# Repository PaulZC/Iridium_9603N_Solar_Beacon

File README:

########################################
# Iridium 9603N Solar Beacon Prototype #
########################################

A breadboard prototype for a Solar Powered Iridium 9603N Beacon.

Power for the beacon is provided by a PowerFilm MPT3.6-150 solar panel.

Power for the Iridium 9603N is provided by a Linear Technology LTC3225EDDB supercapacitor charger.

See Iridium_9603N_Solar_Beacon_Prototype.pdf for a full description of the project:
https://github.com/PaulZC/Iridium_9603N_Solar_Beacon/blob/master/Iridium_9603N_Solar_Beacon_Prototype.pdf

The Arduino code can be found in Iridium9603NSolarBeaconPrototype
https://github.com/PaulZC/Iridium_9603N_Solar_Beacon/tree/master/Iridium9603NSolarBeaconPrototype

A Fritzing hook-up diagram can be found in Iridium_9603N_Solar_Beacon_Prototype_Fritzing.png
https://github.com/PaulZC/Iridium_9603N_Solar_Beacon/blob/master/Iridium_9603N_Solar_Beacon_Prototype_Fritzing.png

This project is distributed under a Creative Commons Attribution + Share-alike (BY-SA) licence.

Enjoy!

Paul

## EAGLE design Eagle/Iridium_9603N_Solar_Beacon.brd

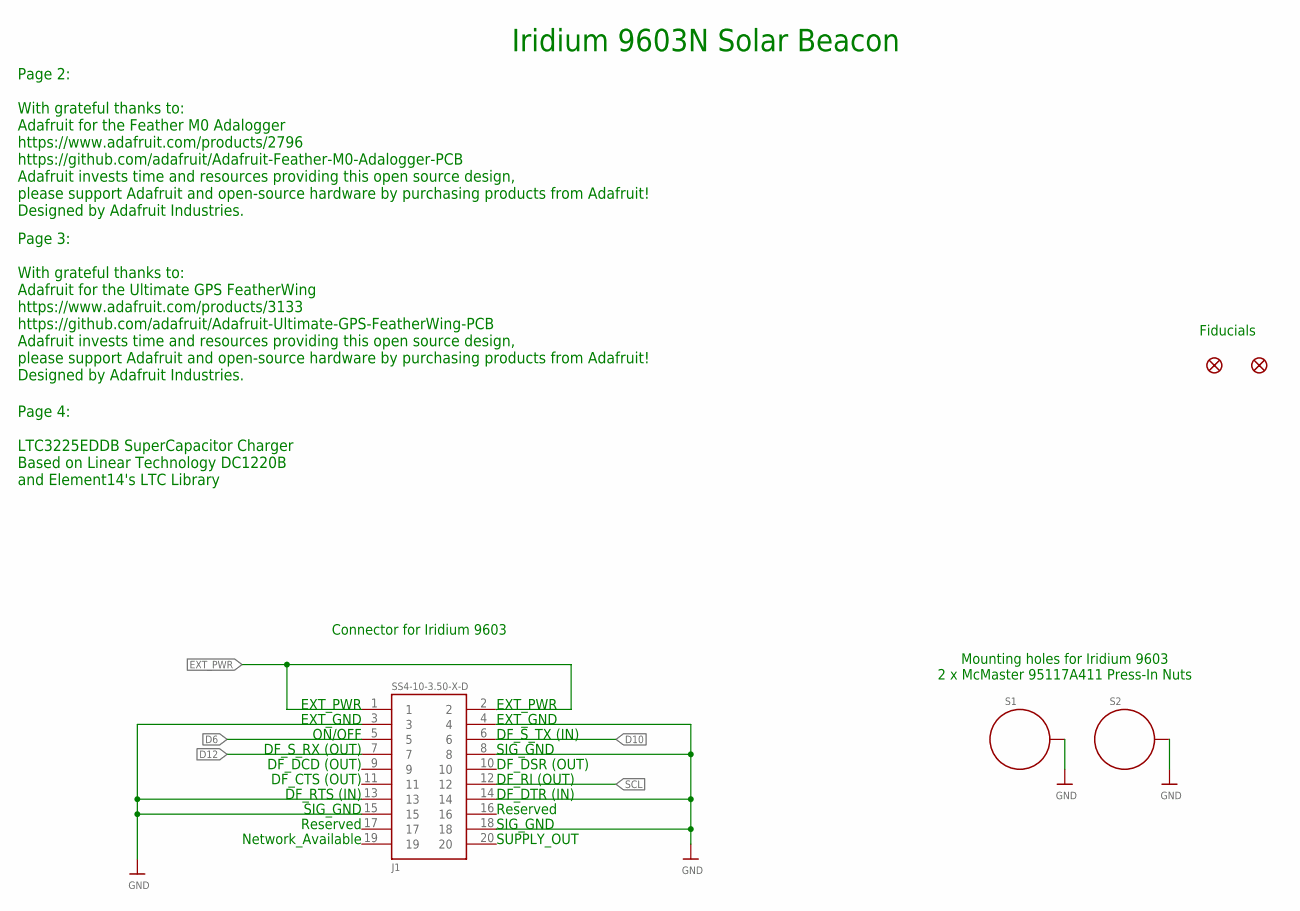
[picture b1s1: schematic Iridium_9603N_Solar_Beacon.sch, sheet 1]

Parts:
FD1, FD2: FIDUCIAL1X2; FIDUCIAL-1X2
J1: SS4-10-3.50-X-D
S1, S2: STANDOFF_ELECTRICALMCMASTER-95117A411; STANDOFF-ELECTRICAL-MCMASTER-95117A411

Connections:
D6: J1.5; also elsewhere on the board
D10: J1.6; also elsewhere on the board
D12: J1.7; also elsewhere on the board
EXT_PWR: J1.1, J1.2; also elsewhere on the board
GND: J1.3, J1.4, J1.8, J1.13, J1.14, J1.15, J1.18, S1.P1, S2.P1; also elsewhere on the board
SCL: J1.12; also elsewhere on the board

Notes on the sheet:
Connector for Iridium 9603
Mounting holes for Iridium 9603 2 x McMaster 95117A411 Press-In Nuts
Iridium 9603N Solar Beacon
Page 2: With grateful thanks to: Adafruit for the Feather M0 Adalogger https://www.adafruit.com/products/2796 https://github.com/adafruit/Adafruit-Feather-M0-Adalogger-PCB Adafruit invests time and resources providing this open source design, please support Adafruit and open-source hardware by purc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
Page 3: With grateful thanks to: Adafruit for the Ultimate GPS FeatherWing https://www.adafruit.com/products/3133 https://github.com/adafruit/Adafruit-Ultimate-GPS-FeatherWing-PCB Adafruit invests time and resources providing this open source design, please support Adafruit and open-source hardware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
EXT_PWR
EXT_GND
ON/OFF
DF_S_RX (OUT)
DF_DCD (OUT)
DF_CTS (OUT)
DF_RTS (IN)
SIG_GND
Reserved
Network_Available
DF_S_TX (IN)
DF_DSR (OUT)
DF_RI (OUT)
DF_DTR (IN)
SUPPLY_OUT
Page 4: LTC3225EDDB SuperCapacitor Charger Based on Linear Technology DC1220B and Element14's LTC Library
Fiducials

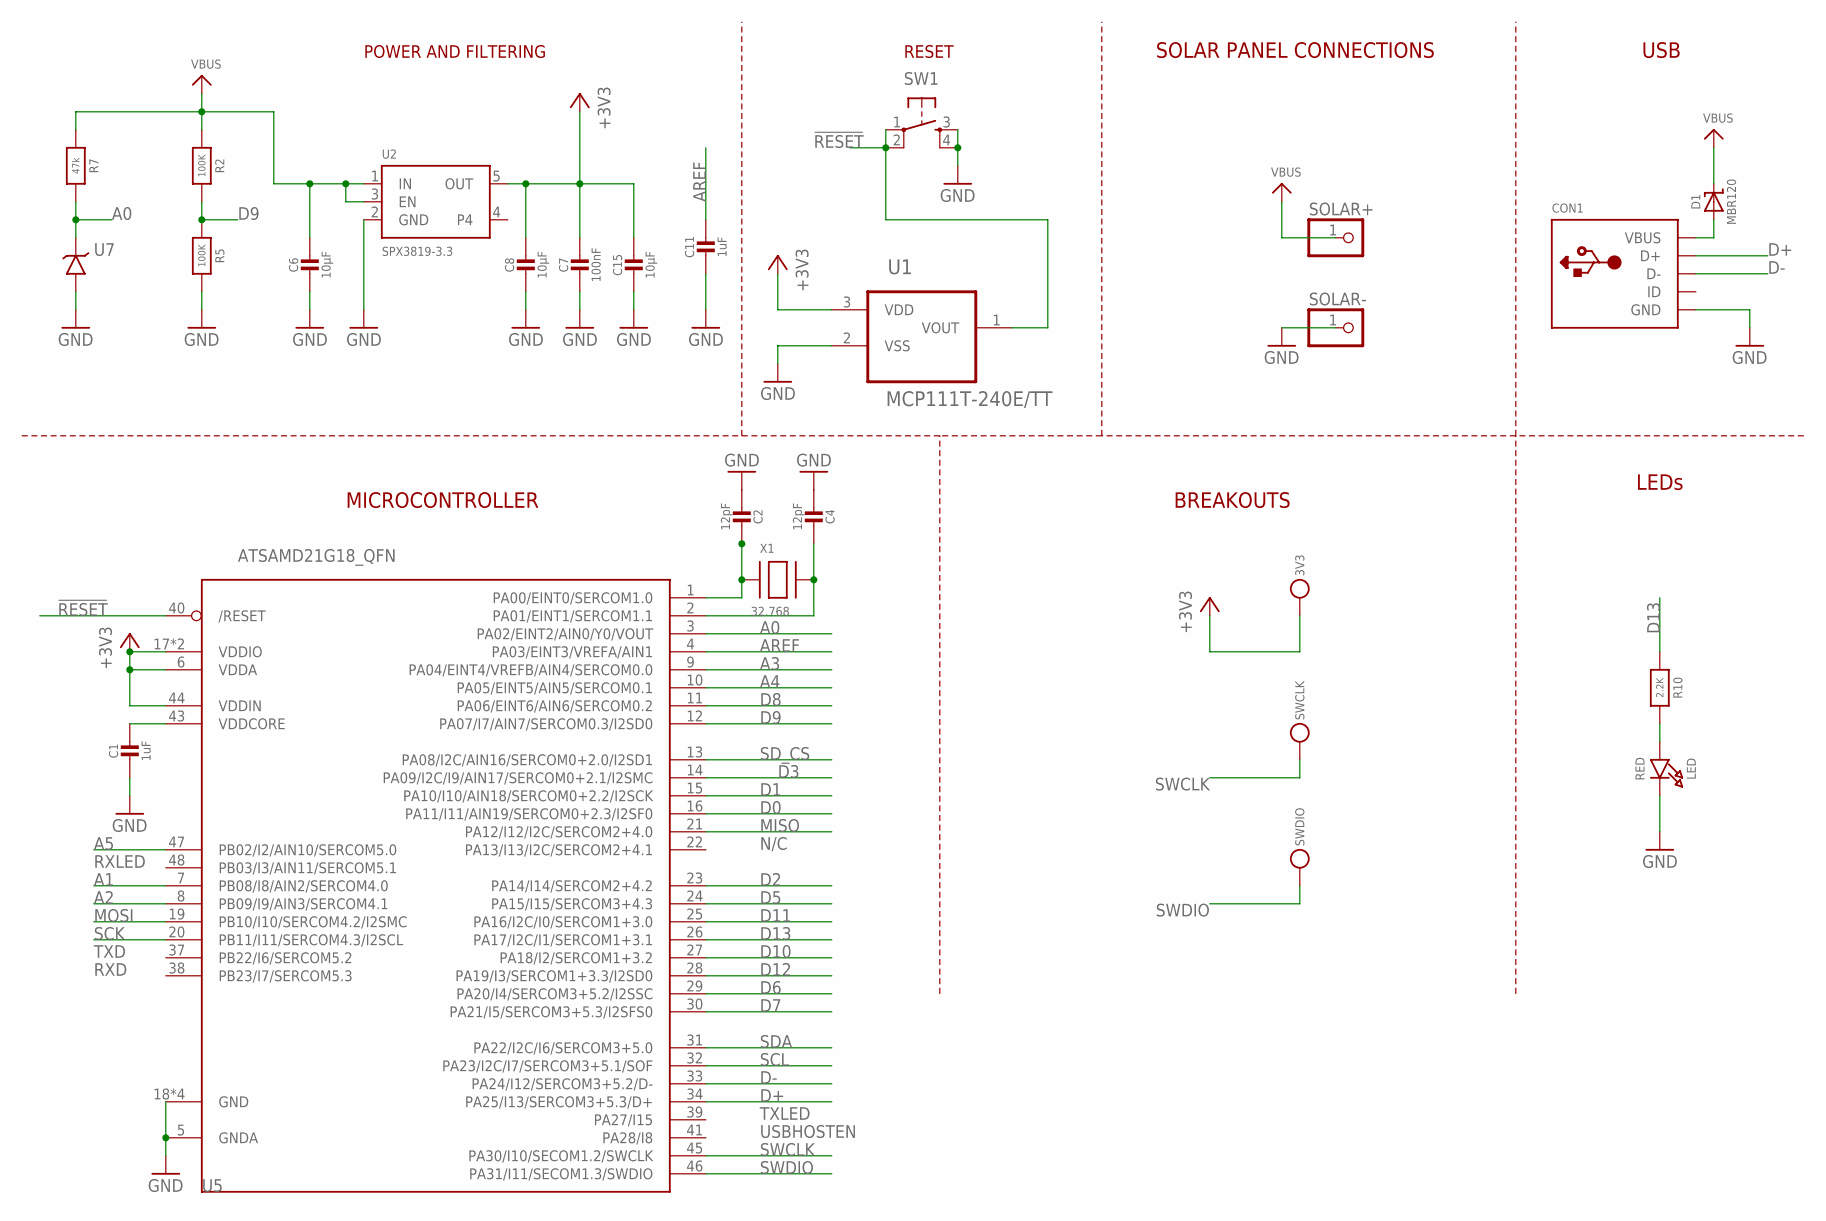
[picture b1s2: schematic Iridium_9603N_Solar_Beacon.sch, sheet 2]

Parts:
3V3: TESTPOINTROUND1.5MM; TESTPOINT_ROUND_1.5MM
C1, C11: 1uF; 0603-NO
C2, C4: 12pF; 0603-NO
C6, C8, C15: 10µF; 0805-NO
C7: 100nF; 0603-NO
CON1: MICROBUILDER_USBFCI_10103594_CORRECTED; MICROBUILDER_FCI_10103594_CORRECTED
D1: MBR120; SOD-123
LED: RED; CHIPLED_0805_NOOUTLINE
R2, R5: 100K; 0603-NO
R7: 47k; 0603-NO
R10: 2.2K; 0603-NO
SOLAR+: PINHD-1X1; 1X01
SOLAR-: PINHD-1X1; 1X01
SW1: SWITCH_SPST_4_PINRECT; TACTILE_SWITCH_SMD_4.6X2.8MM
SWCLK: TESTPOINTROUND1.5MM; TESTPOINT_ROUND_1.5MM
SWDIO: TESTPOINTROUND1.5MM; TESTPOINT_ROUND_1.5MM
U1: MCP111T-240E/TT; SOT95P237X112-3N; MPN MCP111T-240E/TT
U2: SPX3819-3.3; SOT23-5
U5: ATSAMD21G18_QFN; TQFN48_7MM
U7: LT1634-1,25BMCMS8; MSOP8
X1: 32.768; XTAL3215

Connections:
!RESET: SW1.1, SW1.2, U1.1 (VOUT), U5.40 (/RESET)
+3V3: 3V3.P$1, C7.1, C8.1, C15.1, U1.3 (VDD), U2.5 (OUT), U5.6 (VDDA), U5.17 (VDDIO), U5.36 (VDDIO), U5.44 (VDDIN); also elsewhere on the board
A0: R7.2, U5.3 (PA02/EINT2/AIN0/Y0/VOUT), U7.6 (VOUT)
A1: U5.7 (PB08/I8/AIN2/SERCOM4.0); also elsewhere on the board
A2: U5.8 (PB09/I9/AIN3/SERCOM4.1)
A3: U5.9 (PA04/EINT4/VREFB/AIN4/SERCOM0.0)
A4: U5.10 (PA05/EINT5/AIN5/SERCOM0.1)
A5: U5.47 (PB02/I2/AIN10/SERCOM5.0)
AREF: C11.1, U5.4 (PA03/EINT3/VREFA/AIN1)
D0: U5.16 (PA11/I11/AIN19/SERCOM0+2.3/I2SF0); also elsewhere on the board
D1: U5.15 (PA10/I10/AIN18/SERCOM0+2.2/I2SCK); also elsewhere on the board
D2: U5.23 (PA14/I14/SERCOM2+4.2)
D3: U5.14 (PA09/I2C/I9/AIN17/SERCOM0+2.1/I2SMC)
D5: U5.24 (PA15/I15/SERCOM3+4.3); also elsewhere on the board
D6: U5.29 (PA20/I4/SERCOM3+5.2/I2SSC); also elsewhere on the board
D7: U5.30 (PA21/I5/SERCOM3+5.3/I2SFS0)
D8: U5.11 (PA06/EINT6/AIN6/SERCOM0.2)
D9: R2.2, R5.1, U5.12 (PA07/I7/AIN7/SERCOM0.3/I2SD0)
D10: U5.27 (PA18/I2/SERCOM1+3.2); also elsewhere on the board
D11: U5.25 (PA16/I2C/I0/SERCOM1+3.0); also elsewhere on the board
D12: U5.28 (PA19/I3/SERCOM1+3.3/I2SD0); also elsewhere on the board
D13: R10.1, U5.26 (PA17/I2C/I1/SERCOM1+3.1)
D+: CON1.D+, U5.34 (PA25/I13/SERCOM3+5.3/D+)
D-: CON1.D-, U5.33 (PA24/I12/SERCOM3+5.2/D-)
GND: C1.2, C2.2, C4.2, C6.2, C7.2, C8.2, C11.2, C15.2, CON1.BASE@1 (GND), CON1.BASE@2 (GND), CON1.GND, CON1.SPRT@1 (GND), CON1.SPRT@2 (GND), CON1.SPRT@3 (GND), CON1.SPRT@4 (GND), LED.C, R5.2, SOLAR-.1, SW1.3, SW1.4, U1.2 (VSS), U2.2 (GND), U5.5 (GNDA), U5.18 (GND), U5.35 (GND), U5.42 (GND), U5.THERMAL (GND), U7.4 (GND); also elsewhere on the board
MISO: U5.21 (PA12/I12/I2C/SERCOM2+4.0); also elsewhere on the board
MOSI: U5.19 (PB10/I10/SERCOM4.2/I2SMC)
unnamed: LED.A, R10.2
unnamed: C2.1, U5.1 (PA00/EINT0/SERCOM1.0), X1.P$1
unnamed: C4.1, U5.2 (PA01/EINT1/SERCOM1.1), X1.P$2
unnamed: CON1.VBUS, D1.A
SCK: U5.20 (PB11/I11/SERCOM4.3/I2SCL)
SCL: U5.32 (PA23/I2C/I7/SERCOM3+5.1/SOF); also elsewhere on the board
SDA: U5.31 (PA22/I2C/I6/SERCOM3+5.0)
SD_CS: U5.13 (PA08/I2C/AIN16/SERCOM0+2.0/I2SD1)
SWCLK: SWCLK.P$1, U5.45 (PA30/I10/SECOM1.2/SWCLK)
SWDIO: SWDIO.P$1, U5.46 (PA31/I11/SECOM1.3/SWDIO)
VBUS: C6.1, D1.C, R2.1, R7.1, SOLAR+.1, U2.1 (IN), U2.3 (EN); also elsewhere on the board
VDDCORE1: C1.1, U5.43 (VDDCORE)

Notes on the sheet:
POWER AND FILTERING
RESET
N/C
TXLED
USBHOSTEN
RXLED
TXD
RXD
USB
BREAKOUTS
LEDs
MICROCONTROLLER
SOLAR PANEL CONNECTIONS

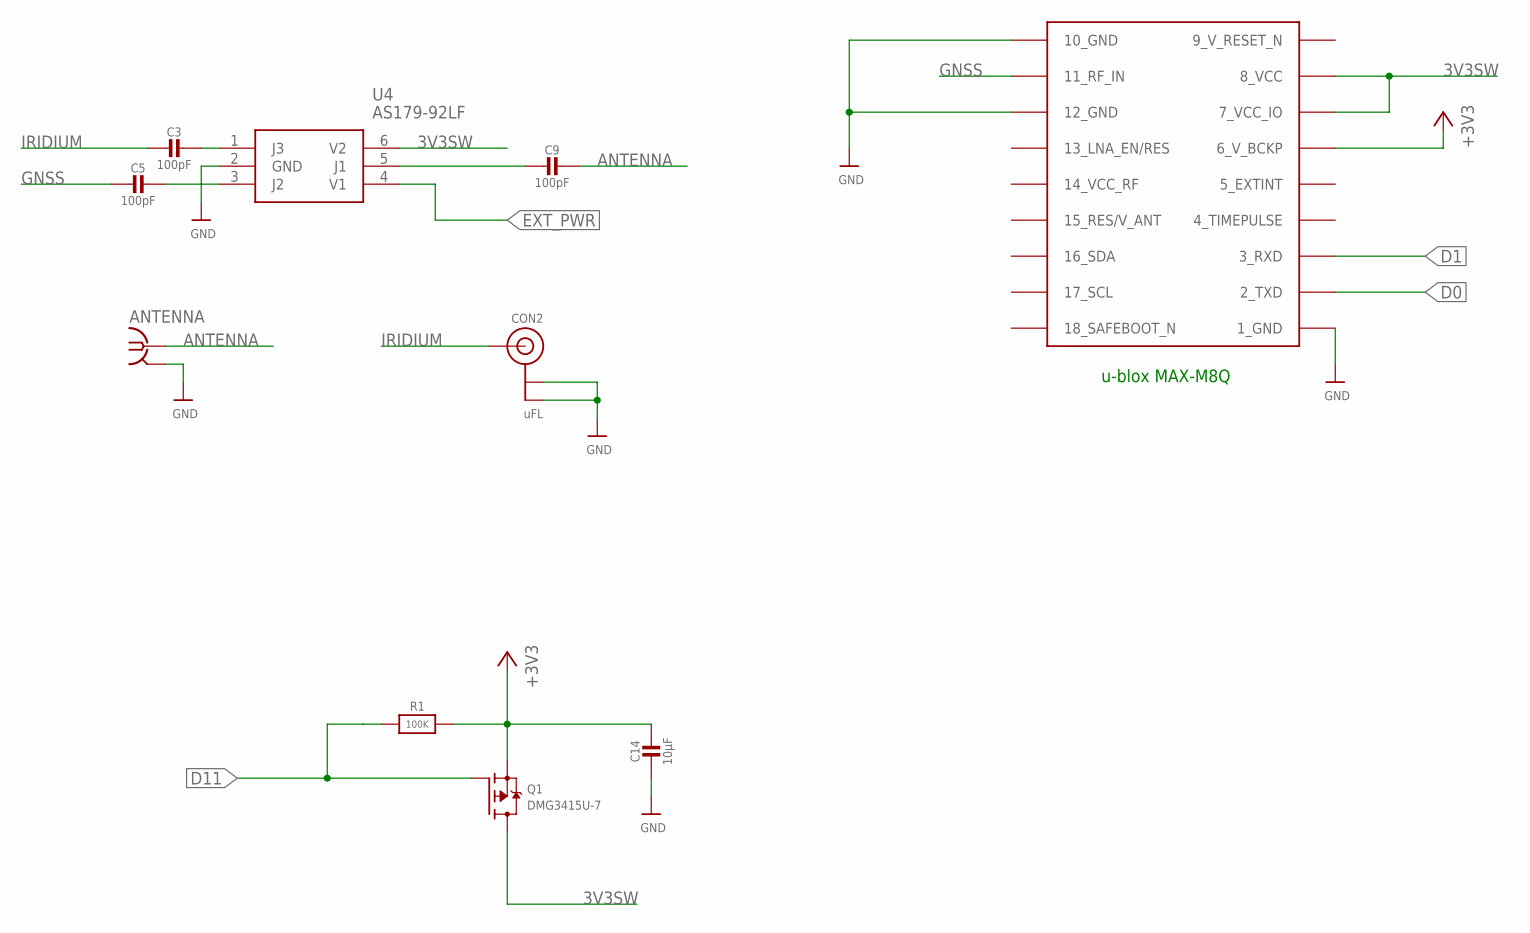
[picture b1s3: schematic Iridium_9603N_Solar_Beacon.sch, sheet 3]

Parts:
ANTENNA: SMA-142-0711-821/826; J502-ND-142-0711-821/826
C3, C5, C9: 100pF; 0603-NO
C14: 10µF; 0805-NO
CON2: uFL; U.FL
Q1: DMG3415U-7; SOT23-WIDE
R1: 100K; 0603-NO
U4: AS179-92LF; SOT65P220X100-6N
U6: MAX-M8

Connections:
3V3SW: Q1.3 (D), U4.6 (V2), U6.7_VCC_IO, U6.8_VCC
9_V_RESET_N: U6.9_RESET_N (9_V_RESET_N)
+3V3: C14.1, Q1.2 (S), R1.2, U6.6_V_BCKP; also elsewhere on the board
ANTENNA: ANTENNA.1, C9.1
D0: U6.2_TXD; also elsewhere on the board
D1: U6.3_RXD; also elsewhere on the board
D11: Q1.1 (G), R1.1; also elsewhere on the board
EXT_PWR: U4.4 (V1); also elsewhere on the board
GND: ANTENNA.G@1 (2), ANTENNA.G@2 (2), ANTENNA.G@3 (2), ANTENNA.G@4 (2), C14.2, CON2.1 (GND), CON2.2 (GND), U4.2 (GND), U6.1_GND, U6.10_GND, U6.12_GND; also elsewhere on the board
GNSS: C5.2, U6.11_RF_IN
IRIDIUM: C3.2, CON2.3 (SIGNAL)
unnamed: C3.1, U4.1 (J3)
unnamed: C5.1, U4.3 (J2)
unnamed: C9.2, U4.5 (J1)

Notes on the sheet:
u-blox MAX-M8Q

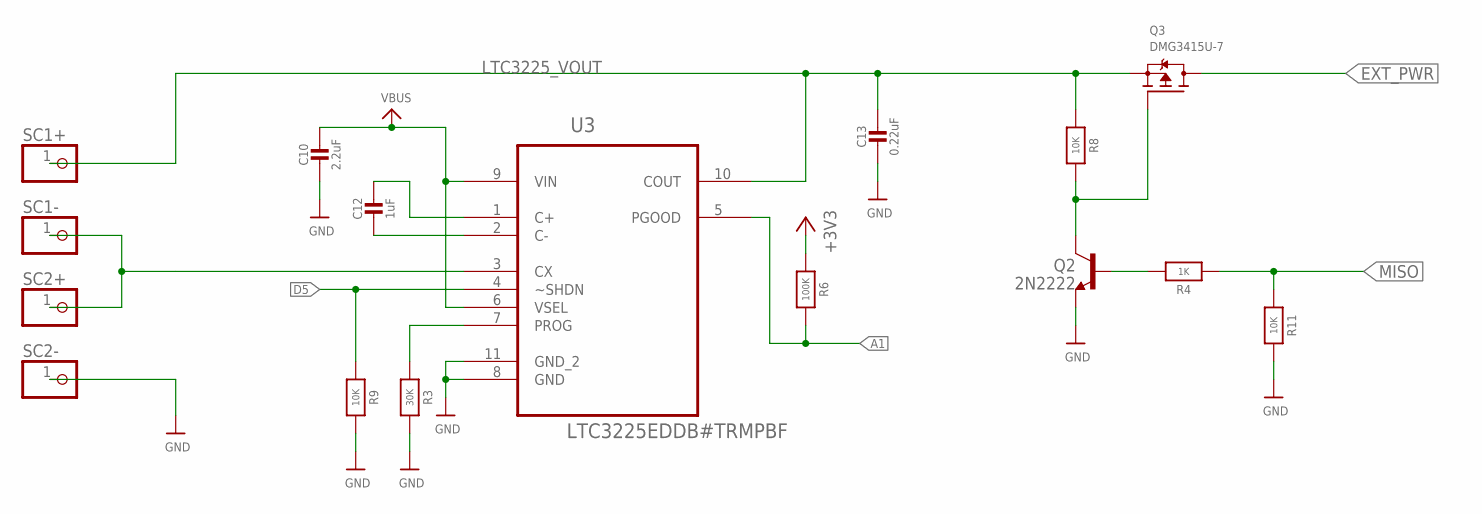
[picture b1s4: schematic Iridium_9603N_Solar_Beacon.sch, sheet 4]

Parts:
C10: 2.2uF; 0603-NO
C12: 1uF; 0603-NO
C13: 0.22uF; 0603-NO
Q2: 2N2222; SOT23-BEC
Q3: DMG3415U-7; SOT23-WIDE
R3: 30K; 0603-NO
R4: 1K; 0603-NO
R6: 100K; 0603-NO
R8, R9, R11: 10K; 0603-NO
SC1+, SC1-, SC2+, SC2-: PINHD-1X1; 1X01
U3: LTC3225EDDB#TRMPBF; DFN300X200-10L

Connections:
+3V3: R6.1; also elsewhere on the board
A1: R6.2, U3.5 (PGOOD); also elsewhere on the board
D5: R9.1, U3.4 (~SHDN); also elsewhere on the board
EXT_PWR: Q3.3 (D); also elsewhere on the board
GND: C10.2, C13.2, Q2.E, R3.2, R9.2, R11.2, SC2-.1, U3.8 (GND), U3.11 (GND_2); also elsewhere on the board
LTC3225_VOUT: C13.1, Q3.2 (S), R8.1, SC1+.1, U3.10 (COUT)
MISO: R4.1, R11.1; also elsewhere on the board
unnamed: SC1-.1, SC2+.1, U3.3 (CX)
unnamed: C12.2, U3.2 (C-)
unnamed: C12.1, U3.1 (C+)
unnamed: R3.1, U3.7 (PROG)
unnamed: Q2.C, Q3.1 (G), R8.2
unnamed: Q2.B, R4.2
VBUS: C10.1, U3.6 (VSEL), U3.9 (VIN); also elsewhere on the board

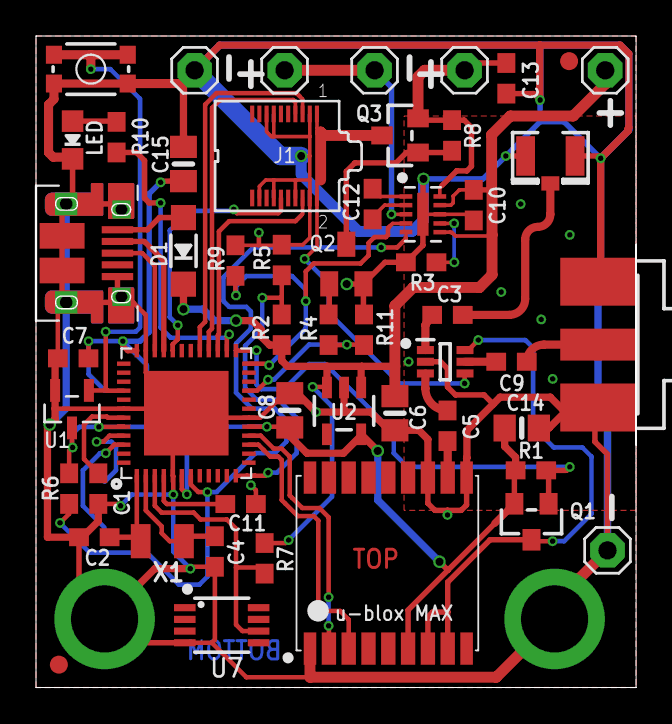
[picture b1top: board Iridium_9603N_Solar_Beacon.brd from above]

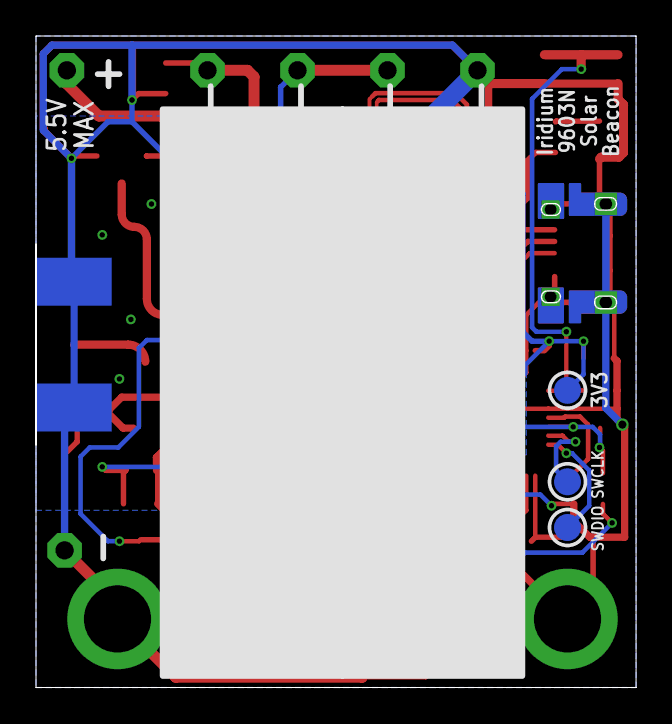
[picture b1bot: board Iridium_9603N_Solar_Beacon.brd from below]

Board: 2 copper layers, 33.3 x 36.1 mm, 57 parts (3 on the bottom side), 42 nets.

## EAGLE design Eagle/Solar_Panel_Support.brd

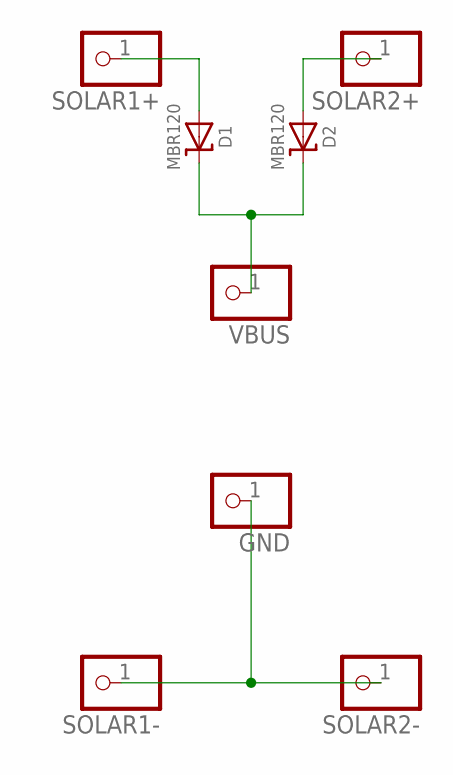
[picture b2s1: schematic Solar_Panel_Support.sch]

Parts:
D1, D2: MBR120; SOD-123
GND: PINHD-1X1; 1X01
SOLAR1+, SOLAR1-, SOLAR2+, SOLAR2-: PINHD-1X1; 1X01
VBUS: PINHD-1X1; 1X01

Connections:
unnamed: D2.A, SOLAR2+.1
unnamed: D1.C, D2.C, VBUS.1
unnamed: GND.1, SOLAR1-.1, SOLAR2-.1
unnamed: D1.A, SOLAR1+.1

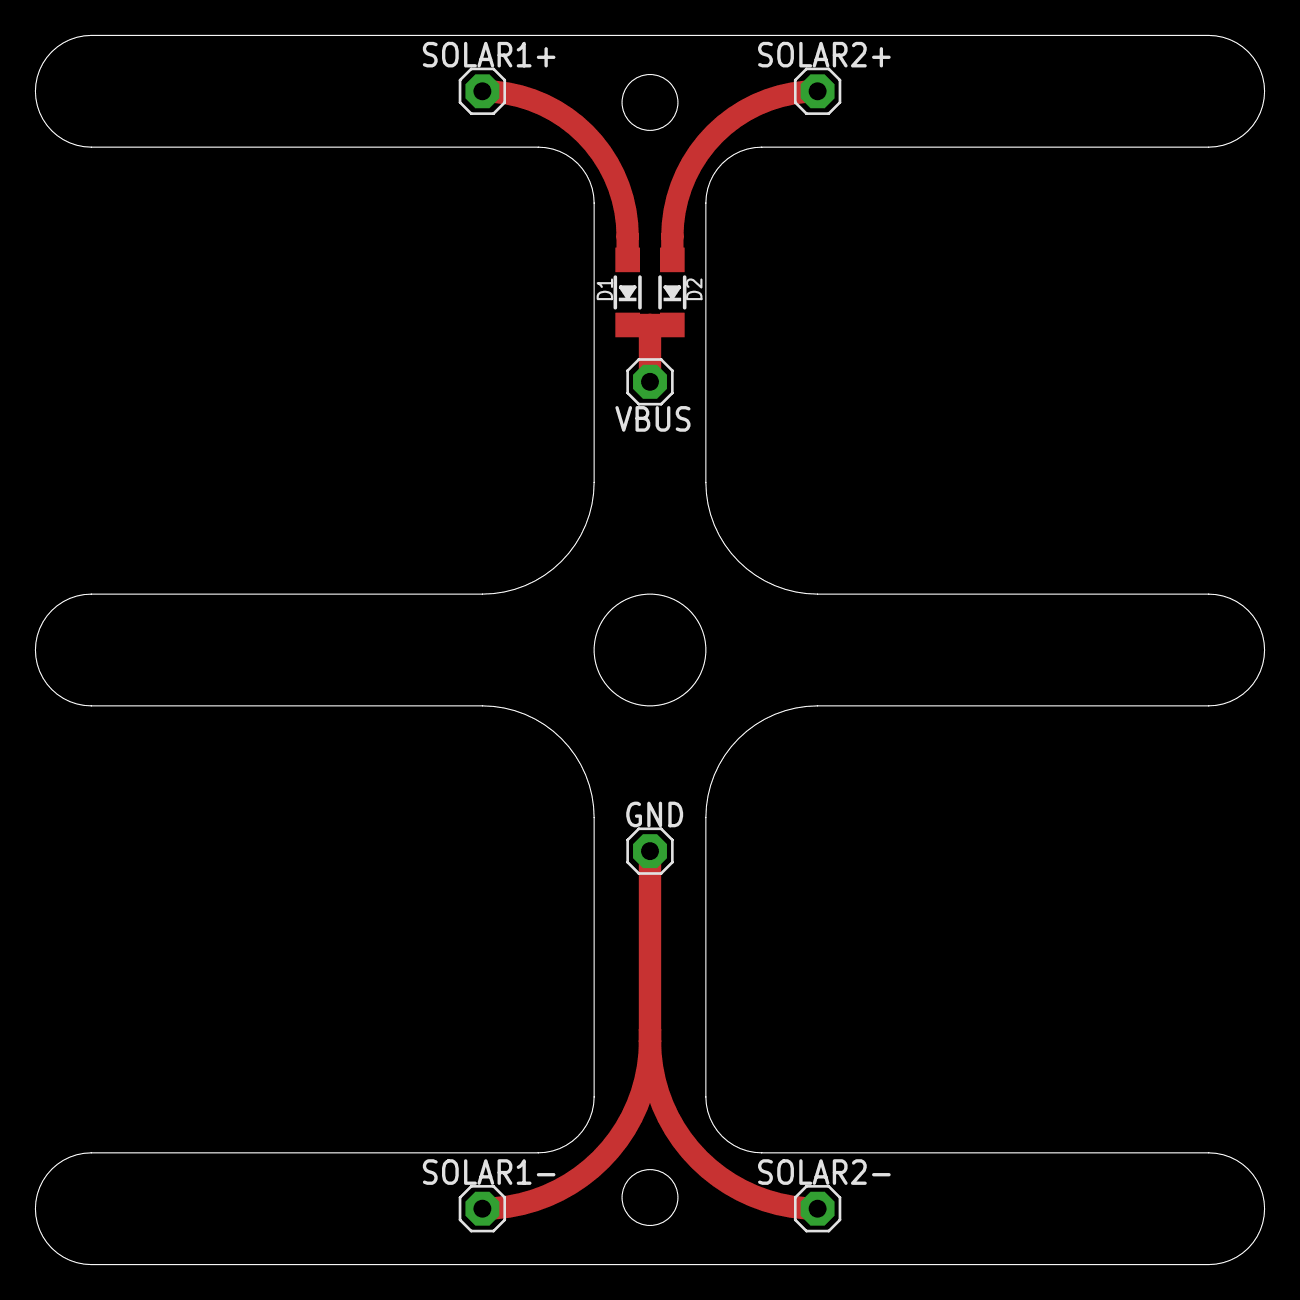
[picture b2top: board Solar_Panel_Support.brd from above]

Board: 2 copper layers, 69.8 x 69.8 mm, 8 parts (0 on the bottom side), 4 nets.

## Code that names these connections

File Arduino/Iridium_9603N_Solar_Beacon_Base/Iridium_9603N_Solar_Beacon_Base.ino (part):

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// Code will be accessed via the Arduino IDE Serial Monitor - or - matching Python code.

// GNSS / Iridium antenna switching is via a Skyworks AS179-92LF RF Switch
// Switching is performed by applying either EXT_PWR or 3V3SW to the AS179's V1 and V2 pins
// EXT_PWR is the 5.3V power rail for the 9603N (switched via Q2 and Q3, enabled by pulling MISO/D22 high)
// 3V3SW is the 3.3V power rail for the MAX-M8Q (switched via Q1, enabled by pulling D11 low)
// Take great care to make sure EXT_PWR and 3V3SW are not enabled at the same time!
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#define ssGPS Serial1 // Use M0 Serial1 to interface to the MAX-M8Q

// Leave the "#define GALILEO" uncommented to use: GPS + Galileo + GLONASS + SBAS
// Comment the "#define GALILEO" out to use the default u-blox M8 GNSS: GPS + SBAS + QZSS + GLONASS
#define GALILEO

// Set Nav Mode to Portable
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
static const int LTC3225shutdown = 5; // LTC3225 ~Shutdown on pin D5
static const int LTC3225PGOOD = 15; // LTC3225 PGOOD on pin A1 / D15
static const int Enable_9603N = 22; // 9603N Enable (enables EXT_PWR via P-MOSFET)
static const int RingIndicator = 21; // Iridium Ring Indicator connected to D21
static const int IridiumSleepPin = 6; // Iridium Sleep connected to D6
IridiumSBD isbd(ssIridium, IridiumSleepPin); // This should disable the 9603
TinyGPS tinygps;
static const int ledPin = 13; // WB2812B + Red LED on pin D13
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  digitalWrite(GPS_EN, GPS_ON); // Enable the GPS
  
  pinMode(IridiumSleepPin, OUTPUT); // The call to IridiumSBD should have done this - but just in case
  digitalWrite(IridiumSleepPin, LOW); // Disable the Iridium 9603
  pinMode(RingIndicator, INPUT_PULLUP); // Define an input for the Iridium 9603 Ring Indicator signal

  pinMode(ledPin, OUTPUT); // LED
  digitalWrite(ledPin, LOW); // Disable the LED
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      isbd.sleep(); // Put 9603 to sleep
      delay(1000);
      
      digitalWrite(IridiumSleepPin, LOW); // Disable the Iridium 9603N
      digitalWrite(Enable_9603N, LOW); // Disconnect power to the 9603N

      loop_step = menu_choice;
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      isbd.sleep(); // Put 9603 to sleep
      delay(1000);
      
      digitalWrite(IridiumSleepPin, LOW); // Disable the Iridium 9603N
      digitalWrite(Enable_9603N, LOW); // Disconnect power to the 9603N

      loop_step = menu_choice;
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      {
      isbd.sleep(); // Put 9603 to sleep
      delay(1000);
      digitalWrite(IridiumSleepPin, LOW); // Disable the Iridium 9603N
      digitalWrite(Enable_9603N, LOW); // Disconnect power to the 9603N
      digitalWrite(LTC3225shutdown, LOW); // Disable the LTC3225 supercapacitor charger
      digitalWrite(GPS_EN, GPS_OFF); // Disable the GPS
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      isbd.sleep(); // Put 9603 to sleep
      delay(1000);
      
      digitalWrite(IridiumSleepPin, LOW); // Disable the Iridium 9603N
      digitalWrite(Enable_9603N, LOW); // Disconnect power to the 9603N

      loop_step = menu_choice;
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
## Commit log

2017-04-14 :confetti_ball: Added .gitattributes & .gitignore files
2017-04-14 First Release
2017-04-14 Updated the pdf
2018-11-18 Major update for new PCB
2018-12-02 Updated the PCB
    Updated the PCB to improve the ground paths around the SAMD; added extra decoupling capacitors. Minor updates to the Arduino code.
2018-12-03 Connected the Ring Indicator
    Connected the 9603N Ring Indicator to D21 just in case the solar beacon is used as a very compact Beacon Base (powered by USB).
2019-01-17 Corrected the zero width polygons
    Corrected the zero width polygons in the micro USB connector that would have caused problems for OSH Park. Thanks go to Paul Loewen @ usask.ca
2019-01-26 Added LEARN.md, ASSEMBLY.md and extra images
2019-01-26 Minor corrections
2019-01-27 Added the Base code and updated the cover
2019-03-02 Added assembly details for the solar panel support.
2019-03-10 Added the antenna spacer
2019-03-12 Minor tweaks
2019-03-17 Improved the battery voltage sampling
    Improved the battery voltage sampling and PGOOD monitoring after testing the beacon on full solar power.
2019-03-18 Added LED flash info
2019-04-10 Added the citation

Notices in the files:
parts and their libraries:
microbuilder: This work is placed in the public domain, and may be freely used for commercial and non-commercial work with the following conditions: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
SparkFun-Electromechanical: Licensing: Creative Commons ShareAlike 4.0 International - https://creativecommons.org/licenses/by-sa/4.0
